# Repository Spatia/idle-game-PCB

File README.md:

# Idle Game PCB

The purpose of this project is to make an Idle/Incremental game from the PCB to the software.

## Hardware Part
TLDR: STM32 with buttons and analogical thumbpad joystick

### Core parts
- MCU: STM32F401 (RET6) in LQFP64
- PMS: BQ24075RGT in QFN16
- Flash: 128Mbits - SPI

### Input/Output
- 1 320x240 Screen ILI9341 based - SPI
- 6 Buttons for game control - GPIO
- 2 Buttons for screen/power control - GPIO
- 1 Button for BOOT0
- 1 PSP Thumbpad - ADC
- 1 USB-C for DFU and Charging battery

### PCB Architecture
1. Front: I/O and STM32
2. In1: Ground
3. In2: Power (3v3 and VBAT)
4. Back: Battery and Power management

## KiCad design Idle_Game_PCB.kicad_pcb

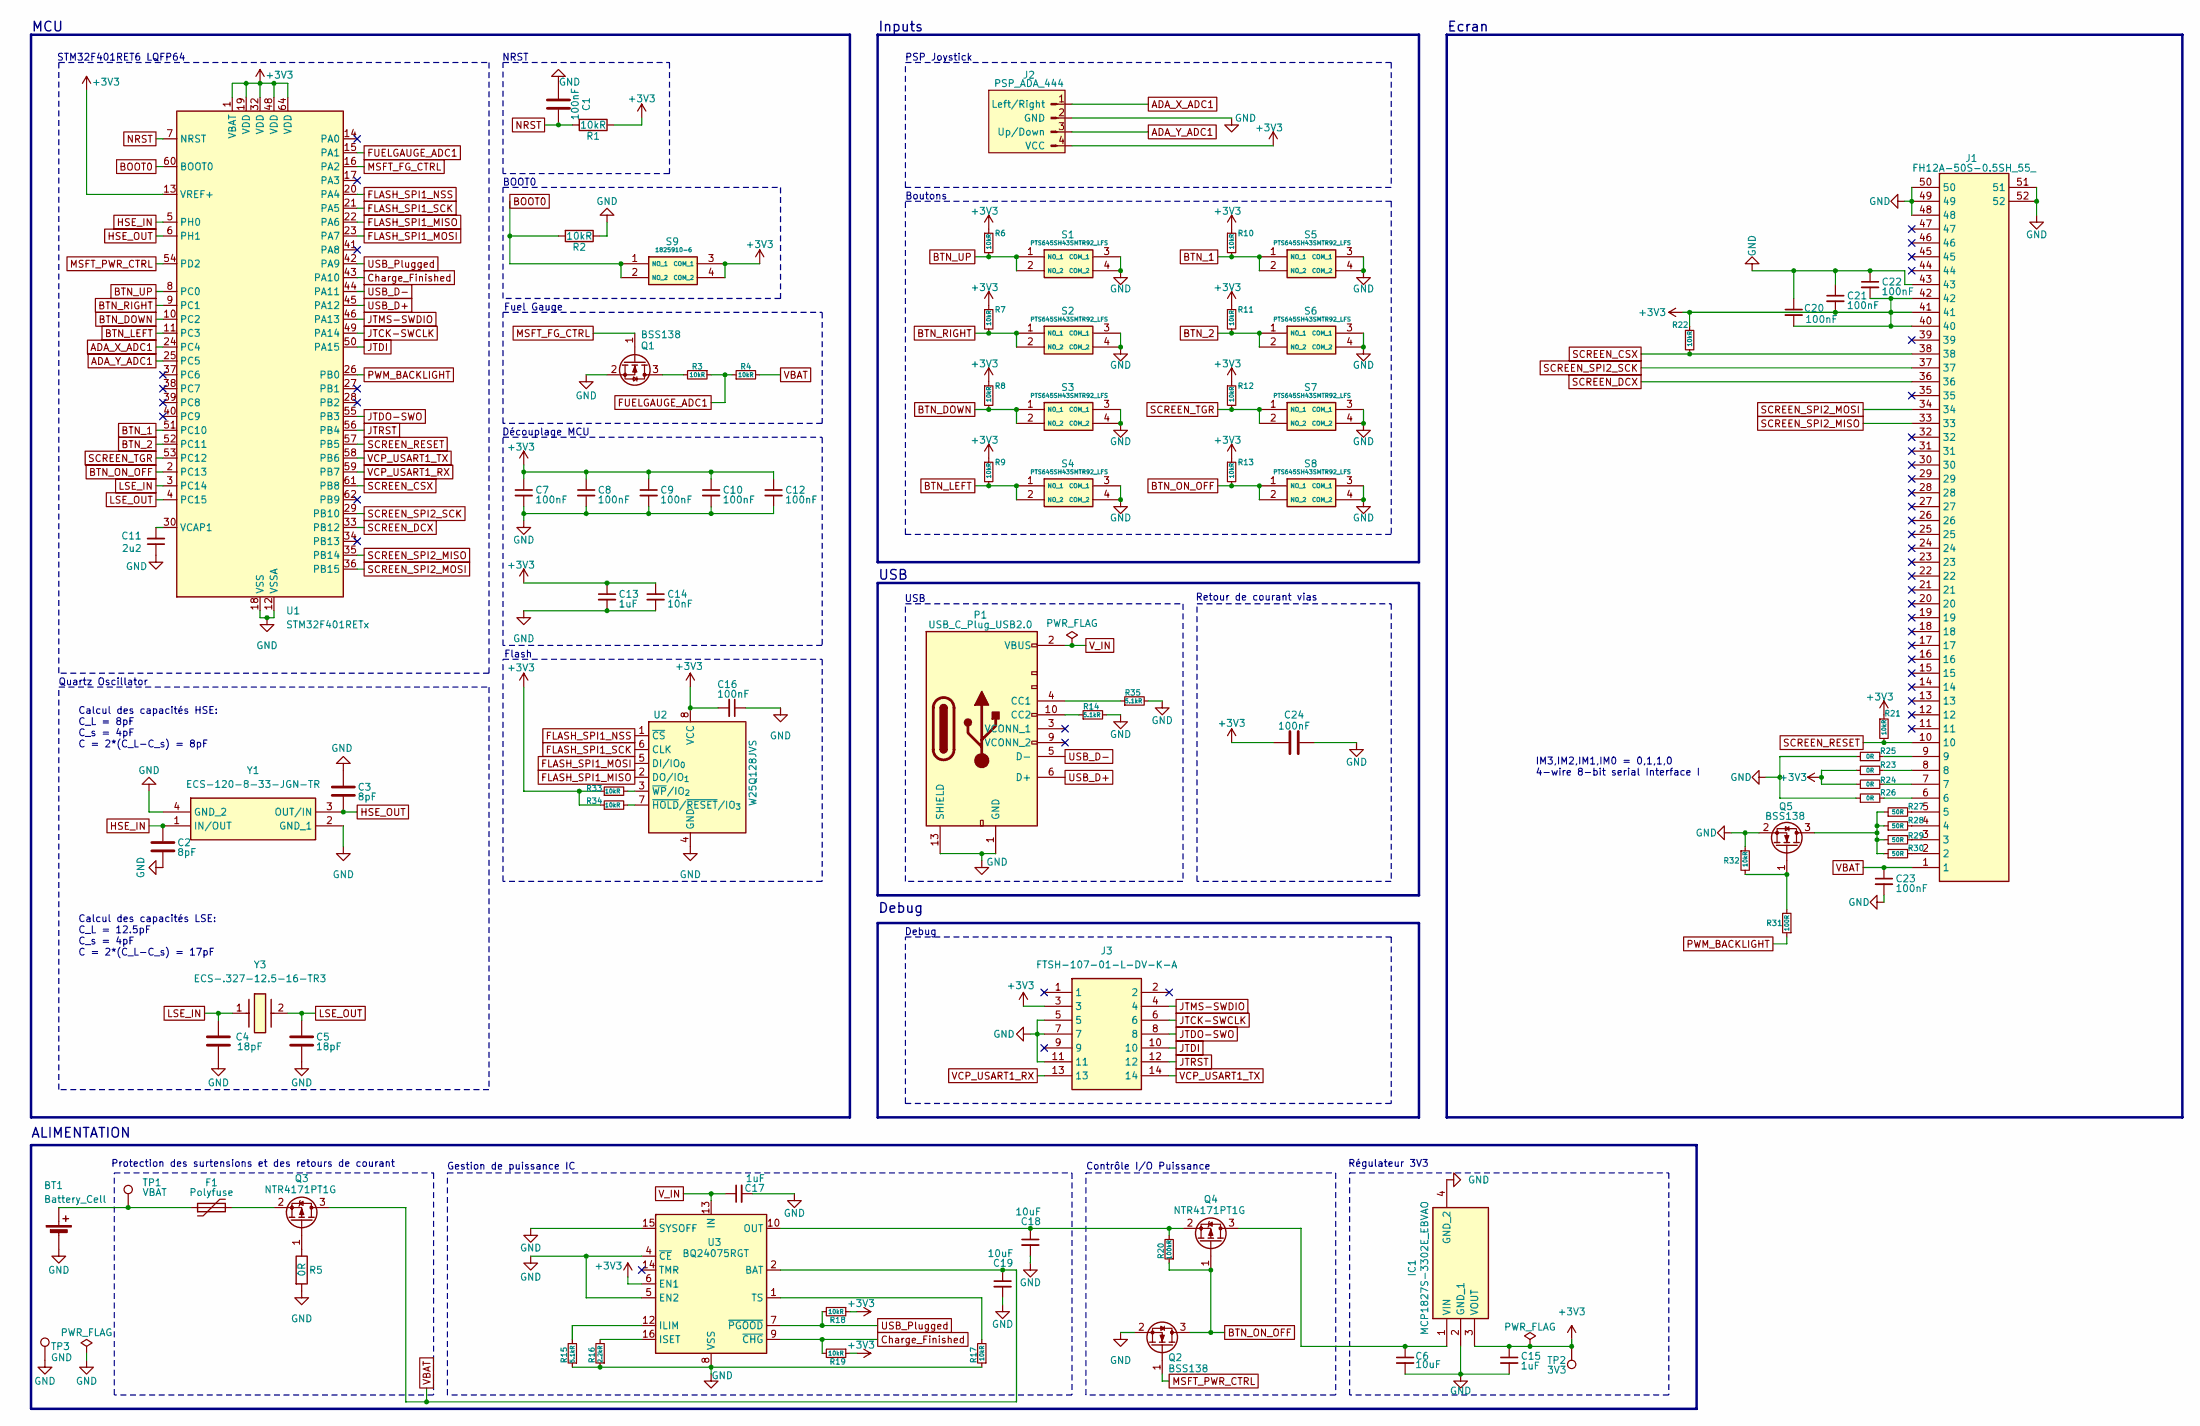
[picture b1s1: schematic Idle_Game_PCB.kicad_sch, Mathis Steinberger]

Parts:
BT1: Battery_Cell; JST_PH_S2B-PH-K_1x02_P2.00mm_Horizontal
C1, C16, C20, C21, C22, C23, C24: 100nF; C_0805_2012Metric_Pad1.18x1.45mm_HandSolder
C2, C3: 8pF; C_0805_2012Metric_Pad1.18x1.45mm_HandSolder
C4, C5: 18pF; C_0805_2012Metric_Pad1.18x1.45mm_HandSolder
C6, C18, C19: 10uF; C_0805_2012Metric_Pad1.18x1.45mm_HandSolder
C7, C8, C9, C10, C12: 100nF; C_0603_1608Metric_Pad1.08x0.95mm_HandSolder
C11: 2u2; C_0603_1608Metric_Pad1.08x0.95mm_HandSolder
C13: 1uF; C_0603_1608Metric_Pad1.08x0.95mm_HandSolder
C14: 10nF; C_0603_1608Metric_Pad1.08x0.95mm_HandSolder
C15, C17: 1uF; C_0805_2012Metric_Pad1.18x1.45mm_HandSolder
F1: Polyfuse; 1812L010DR
IC1: MCP1827S-3302E_EBVAO; MCP1827S3302EEBVAO; Manufacturer_Part_Number MCP1827S-3302E/EBVAO
J1: FH12A-50S-0.5SH_55_; FH1250S05SH55_Mirrored; Mouser Part Number 798-FH12A-50S0.5SH55
J2: PSP_ADA_444; PSPADA444
J3: FTSH-107-01-L-DV-K-A; FTSH-107-XX-YYY-DV-K-A; Mouser Part Number 200-FTSH10701LDVKA
P1: USB_C_Plug_USB2.0; USB_Receptacle
Q1, Q2, Q5: BSS138; SOT-23
Q3, Q4: NTR4171PT1G; SOT-23
R1: 10kR; R_0805_2012Metric
R2, R3, R4, R6, R7, R8, R9, R10, R11, R12, R13, R17, R21, R22, R32, R33, R34: 10kR; R_0805_2012Metric_Pad1.20x1.40mm_HandSolder
R5, R23, R24, R25, R26: 0R; R_0805_2012Metric_Pad1.20x1.40mm_HandSolder
R14, R15, R35: 5.1kR; R_0805_2012Metric_Pad1.20x1.40mm_HandSolder
R16: 2.2kR; R_0805_2012Metric_Pad1.20x1.40mm_HandSolder
R18, R19: 10kR; R_0603_1608Metric_Pad0.98x0.95mm_HandSolder
R20: 100kR; R_0805_2012Metric_Pad1.20x1.40mm_HandSolder
R27, R28, R29, R30: 50R; R_0805_2012Metric_Pad1.20x1.40mm_HandSolder
R31: 100R; R_0805_2012Metric_Pad1.20x1.40mm_HandSolder
S1, S2, S3, S4, S5, S6, S7, S8: PTS645SH43SMTR92_LFS; PTS645SH43SMTR92LFS; Manufacturer_Part_Number PTS645SH43SMTR92 LFS
S9: 1825910-6; 18259106; Manufacturer_Part_Number PTS645SH43SMTR92 LFS
TP1: VBAT; TestPoint_Pad_D2.0mm
TP2: 3V3; TestPoint_Pad_D2.0mm
TP3: GND; TestPoint_Pad_D2.0mm
U1: STM32F401RETx; LQFP-64_10x10mm_P0.5mm
U2: W25Q128JVS; SOIC-8_5.3x5.3mm_P1.27mm
U3: BQ24075RGT; VQFN-16-1EP_3x3mm_P0.5mm_EP1.6x1.6mm
Y1: ECS-120-8-33-JGN-TR; ECS-120-8-33-JGN-TR_ECS; Mouser Part Number 520-120-8-33-JGNT
Y3: ECS-.327-12.5-16-TR3; ECS32712534RRTR; Mouser Part Number 520-ECS.32712.516TR3

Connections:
+3V3: C7.1, C8.1, C9.1, C10.1, C12.1, C13.1, C14.1, C15.1, C16.2, C20.2, C21.2, C22.2, C24.1, IC1.3 (VOUT), J1.40, J1.41, J1.42, J2.4 (VCC), J3.3, R1.1, R6.1, R7.1, R8.1, R9.1, R10.1, R11.1, R12.1, R13.1, R18.1, R19.1, R21.1, R22.1, R23.1, R24.1, R33.1, R34.1, S9.3 (COM_1), S9.4 (COM_2), TP2.1 (1_1), U1.1 (VBAT), U1.13 (VREF+), U1.19 (VDD), U1.32 (VDD), U1.48 (VDD), U1.64 (VDD), U2.8 (VCC), U3.6 (EN1)
ADA_X_ADC1: J2.1 (Left/Right), U1.24 (PC4)
ADA_Y_ADC1: J2.3 (Up/Down), U1.25 (PC5)
BOOT0: R2.2, S9.1 (NO_1), S9.2 (NO_2), U1.60 (BOOT0)
BTN_1: R10.2, S5.1 (NO_1), S5.2 (NO_2), U1.51 (PC10)
BTN_2: R11.2, S6.1 (NO_1), S6.2 (NO_2), U1.52 (PC11)
BTN_DOWN: R8.2, S3.1 (NO_1), S3.2 (NO_2), U1.10 (PC2)
BTN_LEFT: R9.2, S4.1 (NO_1), S4.2 (NO_2), U1.11 (PC3)
BTN_ON_OFF: Q2.3 (D), Q4.1 (G), R13.2, R20.1, S8.1 (NO_1), S8.2 (NO_2), U1.2 (PC13)
BTN_RIGHT: R7.2, S2.1 (NO_1), S2.2 (NO_2), U1.9 (PC1)
BTN_UP: R6.2, S1.1 (NO_1), S1.2 (NO_2), U1.8 (PC0)
Charge_Finished: R19.2, U1.43 (PA10), U3.9 (~CHG)
FLASH_SPI1_MISO: U1.22 (PA6), U2.2 (DO/IO_{1})
FLASH_SPI1_MOSI: U1.23 (PA7), U2.5 (DI/IO_{0})
FLASH_SPI1_NSS: U1.20 (PA4), U2.1 (~CS)
FLASH_SPI1_SCK: U1.21 (PA5), U2.6 (CLK)
FUELGAUGE_ADC1: R3.1, R4.1, U1.15 (PA1)
GND: BT1.2 (-), C1.1, C2.2, C3.2, C4.2, C5.2, C6.2, C7.2, C8.2, C9.2, C10.2, C11.1, C12.2, C13.2, C14.2, C15.2, C16.1, C17.2, C18.2, C19.2, C20.1, C21.1, C22.1, C23.2, C24.2, IC1.2 (GND_1), IC1.4 (GND_2), J1.43, J1.48, J1.49, J1.50, J1.51, J1.52, J2.2 (GND), J3.5, J3.7, J3.11, P1.1 (GND), P1.12 (GND), P1.13 (SHIELD), P1.14 (SHIELD), P1.15 (SHIELD), P1.16 (SHIELD), Q1.2 (S), Q2.2 (S), Q5.2 (S), R2.1, R5.2, R14.2, R15.1, R16.1, R17.1, R25.1, R26.1, R32.1, R35.2, S1.3 (COM_1), S1.4 (COM_2), S2.3 (COM_1), S2.4 (COM_2), S3.3 (COM_1), S3.4 (COM_2), S4.3 (COM_1), S4.4 (COM_2), S5.3 (COM_1), S5.4 (COM_2), S6.3 (COM_1), S6.4 (COM_2), S7.3 (COM_1), S7.4 (COM_2), S8.3 (COM_1), S8.4 (COM_2), TP3.1 (1_1), U1.12 (VSSA), U1.18 (VSS), U1.31 (VSS), U1.47 (VSS), U1.63 (VSS), U2.4 (GND), U3.4 (~CE), U3.5 (EN2), U3.8 (VSS), U3.15 (SYSOFF), U3.17 (VSS), Y1.2 (GND_1), Y1.4 (GND_2)
HSE_IN: C2.1, U1.5 (PH0), Y1.1 (IN/OUT)
HSE_OUT: C3.1, U1.6 (PH1), Y1.3 (OUT/IN)
JTCK-SWCLK: J3.6, U1.49 (PA14)
JTDI: J3.10, U1.50 (PA15)
JTDO-SWO: J3.8, U1.55 (PB3)
JTMS-SWDIO: J3.4, U1.46 (PA13)
JTRST: J3.12, U1.56 (PB4)
LSE_IN: C4.1, U1.3 (PC14), Y3.1
LSE_OUT: C5.1, U1.4 (PC15), Y3.2
MSFT_FG_CTRL: Q1.1 (G), U1.16 (PA2)
MSFT_PWR_CTRL: Q2.1 (G), U1.54 (PD2)
NRST: C1.2, R1.2, U1.7 (NRST)
unnamed: BT1.1 (+), F1.1, TP1.1 (1_1)
unnamed: C6.1, IC1.1 (VIN), Q4.3 (D)
unnamed: J1.2, R30.2
unnamed: J1.3, R29.2
unnamed: J1.4, R28.2
unnamed: J1.5, R27.2
unnamed: J1.6, R26.2
unnamed: J1.7, R24.2
unnamed: J1.8, R23.2
unnamed: J1.9, R25.2
unnamed: P1.4 (CC1), R35.1
unnamed: P1.10 (CC2), R14.1
unnamed: Q1.3 (D), R3.2
unnamed: Q3.1 (G), R5.1
unnamed: F1.2, Q3.2 (S)
unnamed: C18.1, Q4.2 (S), R20.2, U3.10 (OUT), U3.11 (OUT)
unnamed: Q5.3 (D), R27.1, R28.1, R29.1, R30.1
unnamed: Q5.1 (G), R31.2, R32.2
unnamed: C11.2, U1.30 (VCAP1)
unnamed: R34.2, U2.7 (~HOLD/~RESET/IO_{3})
unnamed: R33.2, U2.3 (~WP/IO_{2})
unnamed: R15.2, U3.12 (ILIM)
unnamed: R16.2, U3.16 (ISET)
unnamed: R17.2, U3.1 (TS)
PWM_BACKLIGHT: R31.1, U1.26 (PB0)
SCREEN_CSX: J1.38, R22.2, U1.61 (PB8)
SCREEN_DCX: J1.36, U1.33 (PB12)
SCREEN_RESET: J1.10, R21.2, U1.57 (PB5)
SCREEN_SPI2_MISO: J1.33, U1.35 (PB14)
SCREEN_SPI2_MOSI: J1.34, U1.36 (PB15)
SCREEN_SPI2_SCK: J1.37, U1.29 (PB10)
SCREEN_TGR: R12.2, S7.1 (NO_1), S7.2 (NO_2), U1.53 (PC12)
USB_D+: P1.6 (D+), P1.8 (D+), U1.45 (PA12)
USB_D-: P1.5 (D-), P1.7 (D-), U1.44 (PA11)
USB_Plugged: R18.2, U1.42 (PA9), U3.7 (~PGOOD)
VBAT: C19.1, C23.1, J1.1, Q3.3 (D), R4.2, U3.2 (BAT), U3.3 (BAT)
VCP_USART1_RX: J3.13, U1.59 (PB7)
VCP_USART1_TX: J3.14, U1.58 (PB6)
V_IN: C17.1, P1.2 (VBUS), P1.11 (VBUS), U3.13 (IN)

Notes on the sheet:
ALIMENTATION
STM32F401RET6 LQFP64
Protection des surtensions et des retours de courant
NRST
MCU
Contrôle I/O Puissance
Régulateur 3V3
Fuel Gauge
USB
Boutons
Gestion de puissance IC
Debug
BOOT0
Inputs
Ecran
Flash
Quartz Oscillator
PSP Joystick
Découplage MCU
Retour de courant vias
IM3,IM2,IM1,IM0 = 0,1,1,0 4-wire 8-bit serial Interface I
Calcul des capacités LSE: C_L = 12.5pF C_s = 4pF C = 2*(C_L-C_s) = 17pF
Calcul des capacités HSE: C_L = 8pF C_s = 4pF C = 2*(C_L-C_s) = 8pF

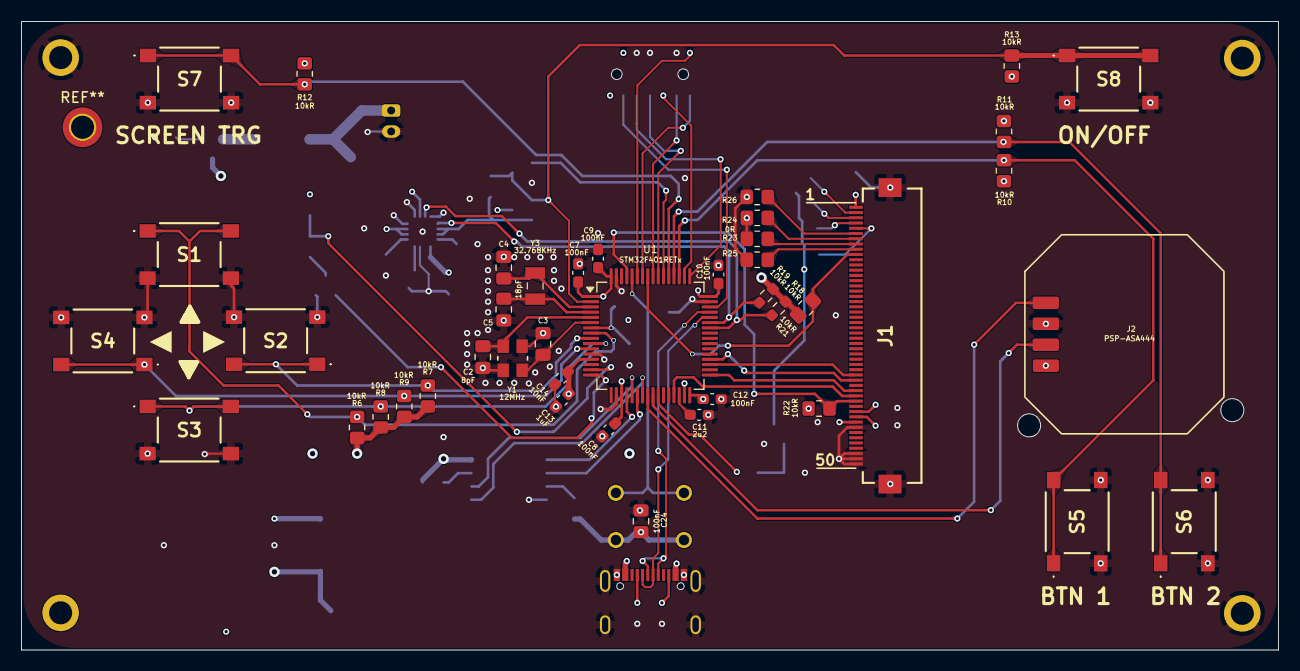
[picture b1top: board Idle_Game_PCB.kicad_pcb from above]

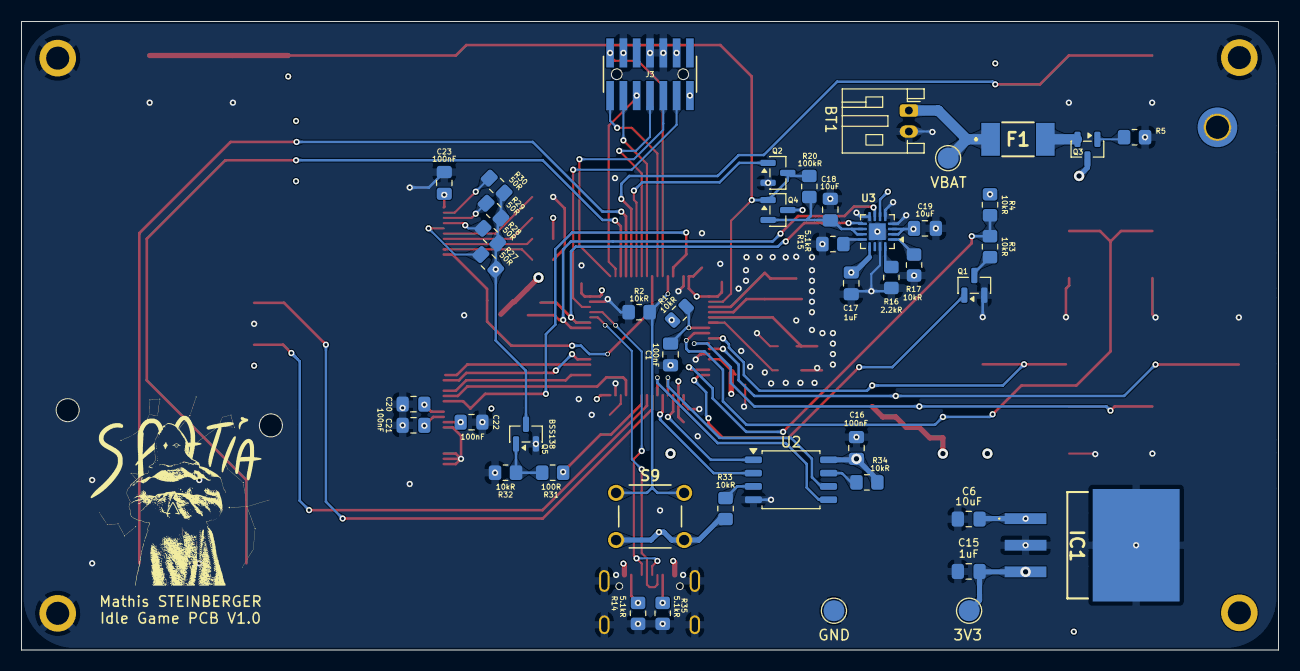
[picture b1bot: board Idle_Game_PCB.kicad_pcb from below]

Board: 4 copper layers, 120.0 x 60.0 mm, 92 parts (45 on the bottom side), 69 nets.

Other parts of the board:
Trou_Bas_Droite: MountingHole_2.2mm_M2
Trou_Bas_Gauche: MountingHole_2.2mm_M2
Trou_Haut_Droite: MountingHole_2.2mm_M2
Trou_Haut_Gauche: MountingHole_2.2mm_M2

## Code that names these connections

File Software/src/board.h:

#ifndef BOARD_H
#define BOARD_H

#include "stm32f401.h"

#define BTN_UP_PORT GPIOC
#define BTN_UP_PIN 0
#define BTN_RIGHT_PORT GPIOC
#define BTN_RIGHT_PIN 1
#define BTN_DOWN_PORT GPIOC
#define BTN_DOWN_PIN 2
#define BTN_LEFT_PORT GPIOC
#define BTN_LEFT_PIN 3
#define BTN_1_PORT GPIOC
#define BTN_1_PIN 10
#define BTN_2_PORT GPIOC
#define BTN_2_PIN 11
#define BTN_TGR_PORT GPIOC
#define BTN_TGR_PIN 12
#define BTN_ONOFF_PORT GPIOC
#define BTN_ONOFF_PIN 13

#define PWR_LATCH_PORT GPIOD
#define PWR_LATCH_PIN 2

#define FG_CTRL_PORT GPIOA
#define FG_CTRL_PIN 2
#define FG_ADC_CHANNEL 1
#define FG_DIVIDER_NUM 2

#define USB_PGOOD_PORT GPIOA
#define USB_PGOOD_PIN 9
#define USB_CHG_PORT GPIOA
#define USB_CHG_PIN 10

#define ADA_X_CHANNEL 14
#define ADA_Y_CHANNEL 15

#define LCD_SPI SPI2_BASE
#define LCD_SCK_PORT GPIOB
#define LCD_SCK_PIN 10
#define LCD_MISO_PORT GPIOB
#define LCD_MISO_PIN 14
#define LCD_MOSI_PORT GPIOB
#define LCD_MOSI_PIN 15
#define LCD_CS_PORT GPIOB
#define LCD_CS_PIN 8
#define LCD_DC_PORT GPIOB
#define LCD_DC_PIN 12
#define LCD_RST_PORT GPIOB
#define LCD_RST_PIN 5

#define BL_PORT GPIOB
#define BL_PIN 0
#define BL_TIM TIM3_BASE
#define BL_AF 2

#define FLASH_SPI SPI1_BASE
#define FLASH_CS_PORT GPIOA
#define FLASH_CS_PIN 4
#define FLASH_SCK_PIN 5
#define FLASH_MISO_PIN 6
#define FLASH_MOSI_PIN 7

/* VCP UART : USART1 sur PB6 / PB7 (AF7) */
#define UART_TX_PORT GPIOB
#define UART_TX_PIN 6
#define UART_RX_PORT GPIOB
#define UART_RX_PIN 7

#endif
